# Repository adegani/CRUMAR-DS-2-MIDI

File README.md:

# CRUMAR-DS-2-MIDI
Add MIDI features to Crumar DS-2 Analog synth using Arduino or bare ATMega328 (with Arduino Bootloader)

This work is published under GNU/GPL.

**NOTE:** This is a WORK IN PROGRESS! Use with caution!

## Abstract
The Crumar DS-2 is a vintage made in Italy analog synth. Unfortunately, it comes without a MIDI IN/OUT capabilityes.
The goal of this project is to add the MIDI port to this wonderful peace of gear by simply substitute the original keyboard decoder board (P-431 on the DS-2 schematics) whit a new one that add MIDI capabilities.

In this repository you can find the Arduino sketch and the schematics of the DS-2_MIDI board and the connection diagram of the Crumar P-431 board.

The DS-2_MIDI board comes in two fashions:

### DS-2 MIDI IN
This simple board provides only MIDI IN to the DS-2. The schematics comes with two microcontroller footprints: one for the Arduino Nano and one for the bare ATMega328 chip.

What you **can do** with this board?
* Receive MIDI NOTE ON/OFF messages

**NOTE:** with this board, the DS-2 keyboard will be **disabled**.

In order to use this variant, please make sure to comment the line
```C
#define DS2_FULL_VARIANT
```
in **config.h**, and refer to the schematic and board *P-431_MIDI_IN_NANO* or *P-431_MIDI_IN_BARE* depending on if you use Arduino Nano or ATMega328 bare chip.

### DS-2 MIDI FULL (under development)
This advanced board provides MIDI IN and OUT to the DS-2. The schematics comes with two microcontroller footprints: one for the Arduino Nano and one for the bare ATMega328 chip.

What you **can do** with this board?
* Receive MIDI NOTE ON/OFF messages
* Send MIDI NOTE ON/OFF from DS-2 keyboard
* Send and Receive MIDI pitch shift messages (TO BE IMPLEMENTED)

**NOTE:** with this board, the DS-2 keyboard are still **usable**.

In order to use this variant, please UNcomment the line
```C
#define DS2_FULL_VARIANT
```
in **config.h**, and refer to the schematic and board *P-431_MIDI_FULL*.

## DISCLAIMER
This is not a commercial work. USE IT AT YOUR OWN RISK. I'm not responsible of any damage to your Arduino / DS-2 or your person.

### Uploading DS-2 sketch using Arduino
1. Upload Arduino ISP sketch to your Arduino
2. Open DS-2 Sketch
3. Select board -> Arduino Duemilanove or Diecimila with processor ATmega328
4. Select Programmer -> Arduino as ISP 
5. Press Upload using programmer (Ctrl+Shift+U)

If you receive a signature error, modify /home/axel/Software/arduino/hardware/tools/avr/etc/avrdude.conf, section m328p, modify the signature 0x1e 0x95 0x0F with 0x1e 0x95 0x14

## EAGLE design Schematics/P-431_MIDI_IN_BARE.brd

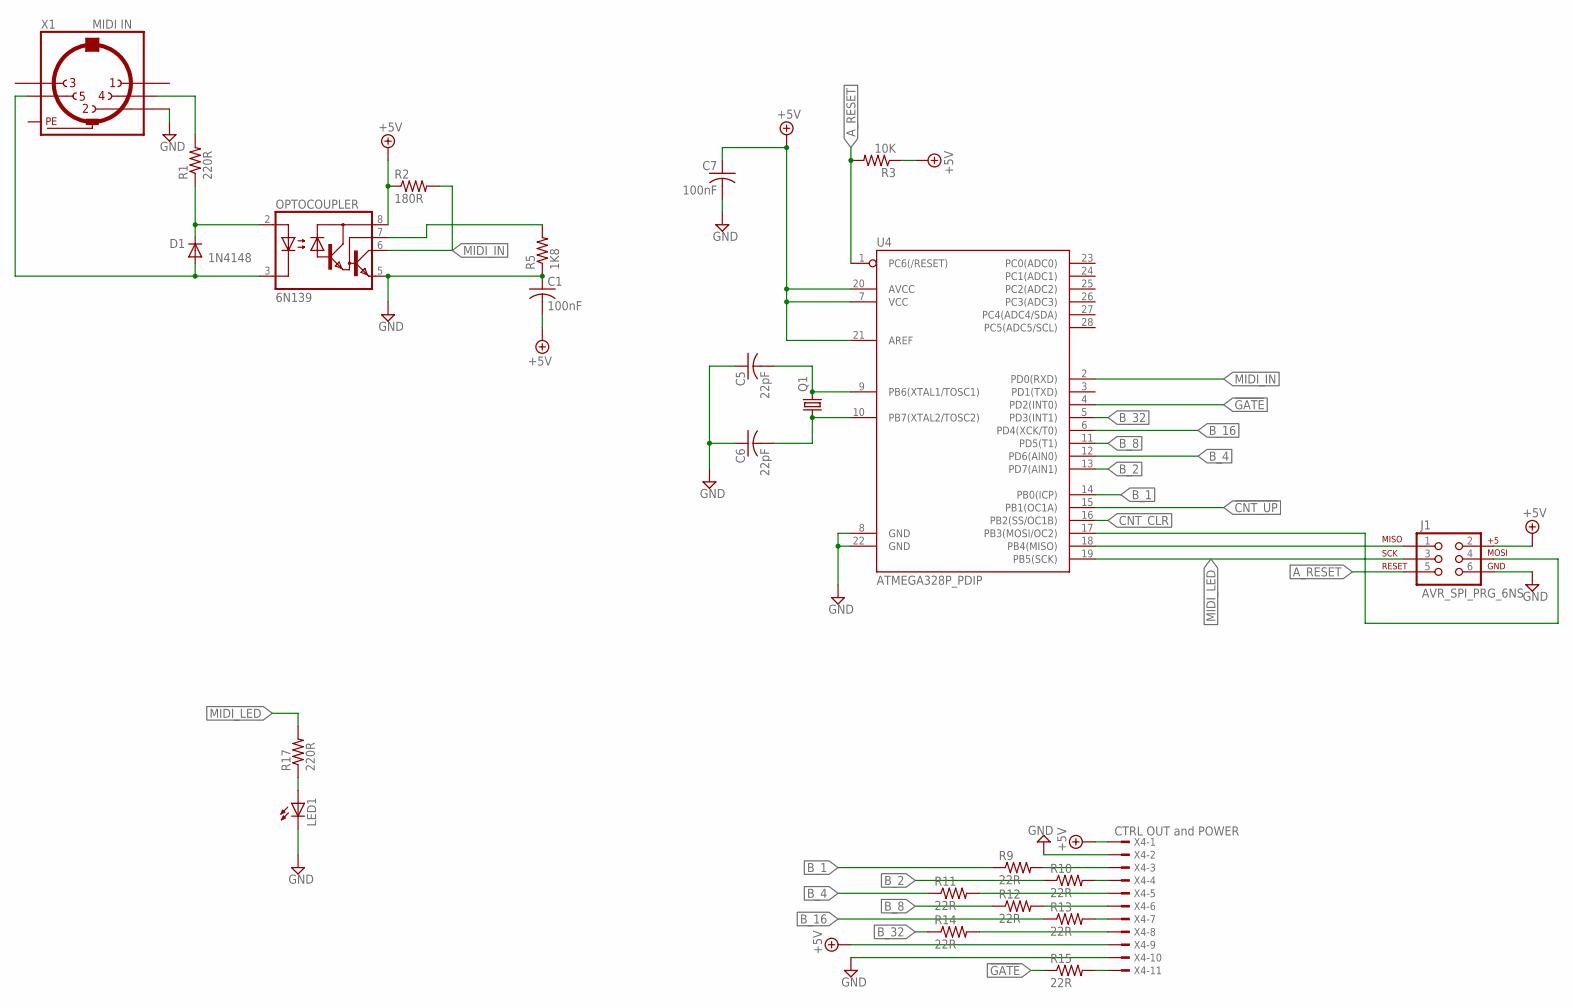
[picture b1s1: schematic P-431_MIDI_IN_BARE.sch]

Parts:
C1, C7: 100nF; C050-025X075
C5, C6: 22pF; C050-025X075
D1: 1N4148; DIODE-1N4148
J1: AVR_SPI_PRG_6NS; 2X3-NS
LED1: LED5MM
OPTOCOUPLER: 6N139; DIL08; MPN 6N138
Q1: CRYSTALHC49S; HC49/S
R1, R17: 220R; 0207/7
R2: 180R; 0207/7
R3: 10K; 0207/7
R5: 1K8; 0207/7
R9, R10, R11, R12, R13, R14, R15: 22R; 0207/7
U4: ATMEGA328P_PDIP; DIL28-3
X1: MIDI IN; MAB5SH
X4: CTRL OUT and POWER; TSW-111-02-S-S-RA

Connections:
!CNT_UP: U4.15 (PB1(OC1A))
!GATE: R15.1, U4.4 (PD2(INT0))
+5V: C1.2, C7.1, J1.2, OPTOCOUPLER.8 (VCC), R2.1, R3.1, U4.7 (VCC), U4.20 (AVCC), U4.21 (AREF), X4.1, X4.9
A_RESET: J1.5, R3.2, U4.1 (PC6(/RESET))
B_1: R9.1, U4.14 (PB0(ICP))
B_2: R10.1, U4.13 (PD7(AIN1))
B_4: R11.1, U4.12 (PD6(AIN0))
B_8: R12.1, U4.11 (PD5(T1))
B_16: R13.1, U4.6 (PD4(XCK/T0))
B_32: R14.1, U4.5 (PD3(INT1))
CNT_CLR: U4.16 (PB2(SS/OC1B))
GND: C1.1, C5.1, C6.1, C7.2, J1.6, LED1.K (C), OPTOCOUPLER.5 (GND), R5.1, U4.8 (GND), U4.22 (GND), X1.2, X4.2, X4.10
MIDI_IN: OPTOCOUPLER.6 (VO), R2.2, U4.2 (PD0(RXD))
MIDI_LED: J1.3, R17.2, U4.19 (PB5(SCK))
unnamed: D1.A, OPTOCOUPLER.3 (C), X1.5
unnamed: D1.C, OPTOCOUPLER.2 (A), R1.1
unnamed: R1.2, X1.4
unnamed: OPTOCOUPLER.7 (VB), R5.2
unnamed: LED1.A, R17.1
unnamed: R9.2, X4.3
unnamed: R10.2, X4.4
unnamed: R11.2, X4.5
unnamed: R12.2, X4.6
unnamed: R13.2, X4.7
unnamed: R14.2, X4.8
unnamed: R15.2, X4.11
unnamed: C5.2, Q1.2, U4.9 (PB6(XTAL1/TOSC1))
unnamed: C6.2, Q1.1, U4.10 (PB7(XTAL2/TOSC2))
PE: X1.PE, X1.PE@ (PE)
POT_DI: J1.1, U4.18 (PB4(MISO))
POT_SCK: J1.4, U4.17 (PB3(MOSI/OC2))

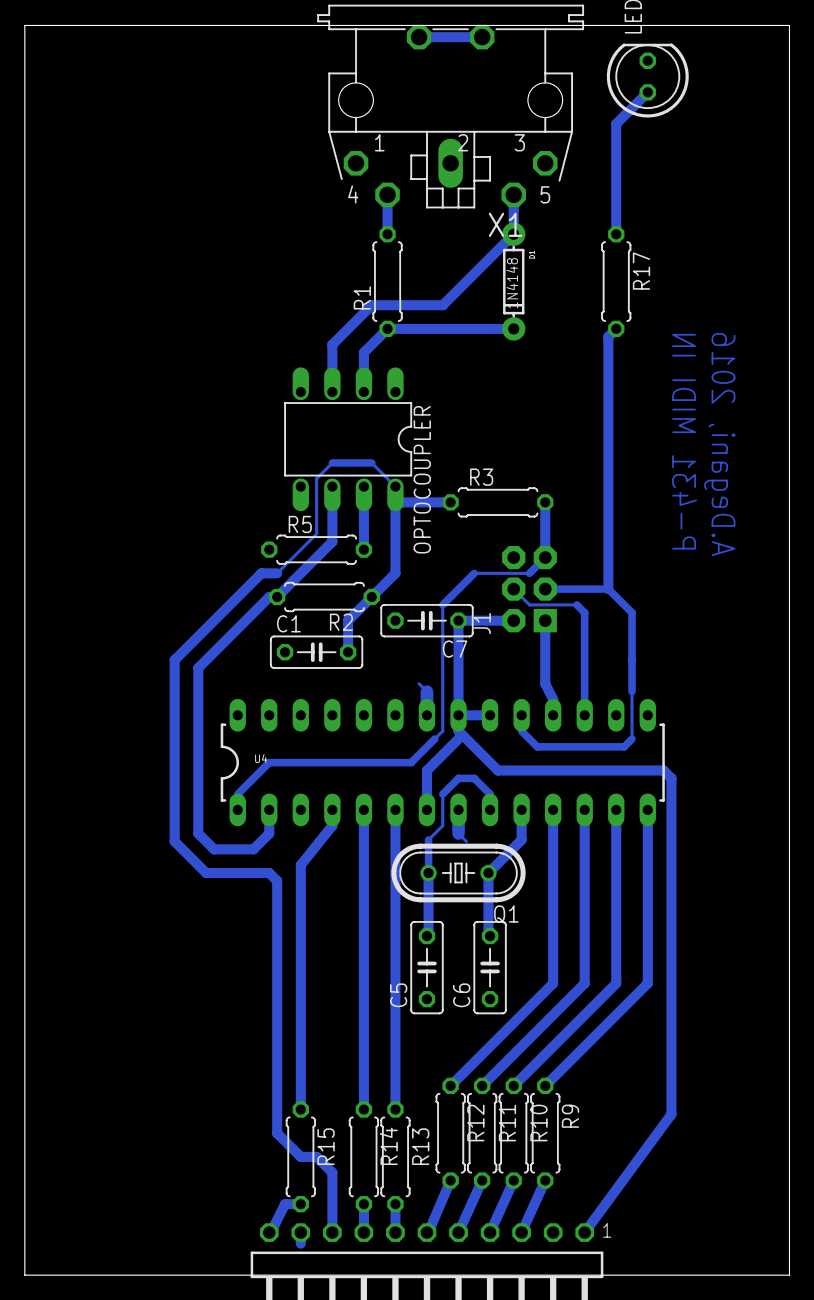
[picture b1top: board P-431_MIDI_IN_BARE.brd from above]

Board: 2 copper layers, 61.6 x 100.6 mm, 24 parts (0 on the bottom side), 29 nets.

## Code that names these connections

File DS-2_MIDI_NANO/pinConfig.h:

/* pinConfig.h
 *  Define Arduino pin names
 *  Author: Alessio Degani, 2016 <alessio.degani@gmail.com>
 */

#ifndef DS2_PINCONFIG_H
#define DS2_PINCONFIG_H

// Configure the ATMega328 pin names

// OUTPUTS to CRUMAR
#define DS2_GATE_NEG  2
#define DS2_32o       3
#define DS2_16o       4
#define DS2_8o        5
#define DS2_4o        6
#define DS2_2o        7
#define DS2_1o        8

// MIDI ports and LED
#define MIDI_LED      13
#define MIDI_OUT      0
#define MIDI_IN       1

// ----- NOT USED IN NANO VERSION -----

// COUNTER
#define COUNT_UP_NEG  9
#define COUNT_CLR     10

// DIGIPOT --> OUT (pitch shifter)
#define POT_SCK       11
#define POT_DI        12

// ANALOG POT --> READ (pitch shifter)
#define PS_POT1       A5
#define PS_POT2       A4
#define PS_POT3       A3

// MUX READ (INPUT from CRUMAR keyboard)
#define K0            A0
#define K1            A1
#define K2            A2

#endif // DS2_PINCONFIG_H

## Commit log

2016-11-05 First commit: preliminary sketch and P-431 schematics
2016-11-05 Added .gitgnore
2016-11-05 deleting some files
2016-11-05 Added first revision of simple MIDI in schematics based on Arduino/Arduino NANO
2016-11-06 Added pin config include
2016-11-06 Added MIDI messages definitions
2016-11-06 Added note list in order to manage more than one NOTE ON/OFF messages at a time
2016-11-07 Some dir and file ranaming
2016-11-07 Added Finite State Machine for managing MIDI messages
2016-11-07 Added MIDI activity LED and MIDI channel filter
2016-11-11 Some code refactoring
2017-01-11 Added reset pullup resistor and fixed resistors value for optocoupler
2017-01-18 Added sketch uploading instructions to README
2017-01-20 Renamed MIDI FSM state names and added some persistence for the MIDI actovity LED
2017-01-24 Changed noteList to a more friendly and effective linked list and fixed note priority bug. Added Gate mode
2017-01-24 Added CC and pitch Wheel support plus some minor bug fix
2017-01-24 Added a GUI written in PureData for P431-MIDI board config via MIDI CCs
2017-01-28 Some code formatting
2017-01-28 Added support for RUNNING STATUS for NOTE ON and Ignore SYSEX messages
2017-01-28 Added semitone transposition controllable by CC
2017-01-28 Add semitone transposition control in GUI
2017-02-08 Added flushing method for resetting the note list, fixed push of alreadi pushed note, fixed pop note when the note was the last of the list
2017-02-08 Fixed: all note/sound off and running status bugs
2017-03-06 Modified config define names for DS-2 parameters
2017-03-06 Midi defs updated
2017-03-06 Modified note linket list wih the one implemented by Francois Best
2017-03-06 New MIDI fsm, optmization and bug fixes

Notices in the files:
parts and their libraries:
SparkFun: Licensing: CC v3.0 Share-Alike You are welcome to use this library for commercial purposes.
SparkFun-DigitalIC: Licensing: Creative Commons ShareAlike 4.0 International - https://creativecommons.org/licenses/by-sa/4.0
